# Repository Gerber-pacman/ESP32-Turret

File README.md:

# ESP32-Turret
Simple Stepper Motor Turret controled by esp32

For this project I have used Esp32 in a arduino uno shape.
For stepper motors I have used 2x ATD5833.
I have included PCB files, its a pretty simple pcb that connects everything nicely.

https://www.printables.com/model/1445566-laser-pointer-robot

If I forgot to include anything please let me know.
Have fun

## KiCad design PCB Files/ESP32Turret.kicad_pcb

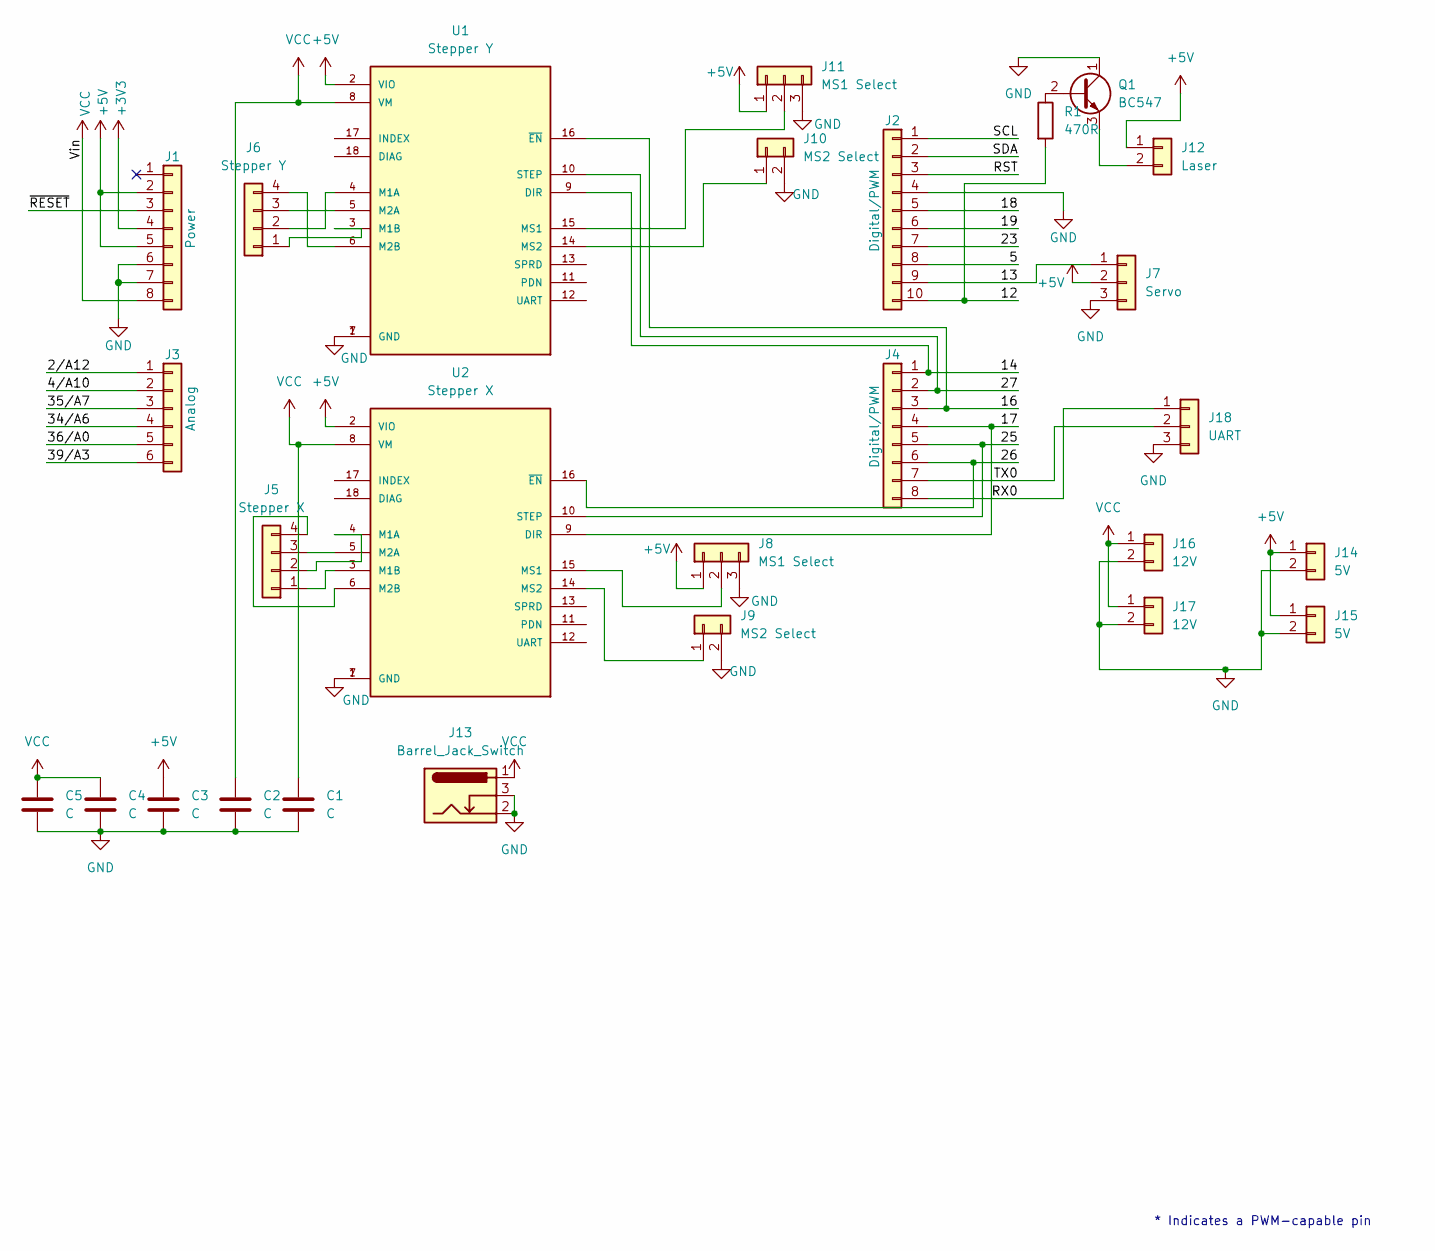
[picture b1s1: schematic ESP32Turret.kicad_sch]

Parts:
C1, C2, C3, C4, C5: C; CP_Radial_D6.3mm_P2.50mm
J1: Power; PinSocket_1x08_P2.54mm_Vertical
J2: Digital/PWM; PinSocket_1x10_P2.54mm_Vertical
J3: Analog; PinSocket_1x06_P2.54mm_Vertical
J4: Digital/PWM; PinSocket_1x08_P2.54mm_Vertical
J5: Stepper X; JST_XH_B4B-XH-A_1x04_P2.50mm_Vertical
J6: Stepper Y; JST_XH_B4B-XH-A_1x04_P2.50mm_Vertical
J7: Servo; PinHeader_1x03_P2.54mm_Vertical
J8, J11: MS1 Select; PinHeader_1x03_P2.54mm_Vertical
J9, J10: MS2 Select; PinHeader_1x02_P2.54mm_Vertical
J12: Laser; JST_EH_B2B-EH-A_1x02_P2.50mm_Vertical
J13: Barrel_Jack_Switch; BarrelJack_GCT_DCJ200-10-A_Horizontal
J14, J15: 5V; JST_EH_B2B-EH-A_1x02_P2.50mm_Vertical
J16, J17: 12V; JST_EH_B2B-EH-A_1x02_P2.50mm_Vertical
J18: UART; PinHeader_1x03_P2.54mm_Vertical
Q1: BC547; TO-92_Inline_Wide
R1: 470R; R_Axial_DIN0207_L6.3mm_D2.5mm_P10.16mm_Horizontal
U1: Stepper Y; MODULE_TMC2209_SILENTSTEPSTICK; PARTREV 1.20
U2: Stepper X; MODULE_TMC2209_SILENTSTEPSTICK; PARTREV 1.20

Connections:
+3V3: J1.4
+5V: C3.1, J1.2, J1.5, J7.2, J8.1, J11.1, J12.1, J14.1, J15.1, U1.2 (VIO), U2.2 (VIO)
/2/A12: J3.1
/4/A10: J3.2
/5: J2.8
/12: J2.10, R1.2
/13: J2.9, J7.1
/14: J4.1, U1.9 (DIR)
/16: J4.3, U1.16 (~EN)
/17: J4.4, U2.9 (DIR)
/18: J2.5
/19: J2.6
/23: J2.7
/25: J4.5, U2.10 (STEP)
/26: J4.6, U2.16 (~EN)
/27: J4.2, U1.10 (STEP)
/34/A6: J3.4
/35/A7: J3.3
/36/A0: J3.5
/39/A3: J3.6
/RST: J2.3
/RX0: J4.8, J18.1
/SCL: J2.1
/SDA: J2.2
/TX0: J4.7, J18.2
/~RESET: J1.3
GND: C1.2, C2.2, C3.2, C4.2, C5.2, J1.6, J1.7, J2.4, J7.3, J8.3, J9.2, J10.2, J11.3, J13.2, J13.3, J14.2, J15.2, J16.2, J17.2, J18.3, Q1.1 (C), U1.1 (GND), U1.7 (GND), U2.1 (GND), U2.7 (GND)
unnamed: J5.1, U2.3 (M1B)
unnamed: J5.2, U2.4 (M1A)
unnamed: J5.3, U2.5 (M2A)
unnamed: J5.4, U2.6 (M2B)
unnamed: J6.1, U1.3 (M1B)
unnamed: J6.2, U1.4 (M1A)
unnamed: J6.3, U1.5 (M2A)
unnamed: J6.4, U1.6 (M2B)
unnamed: J8.2, U2.15 (MS1)
unnamed: J9.1, U2.14 (MS2)
unnamed: J10.1, U1.14 (MS2)
unnamed: J11.2, U1.15 (MS1)
unnamed: J12.2, Q1.3 (E)
unnamed: Q1.2 (B), R1.1
VCC: C1.1, C2.1, C4.1, C5.1, J1.8, J13.1, J16.1, J17.1, U1.8 (VM), U2.8 (VM)

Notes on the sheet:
* Indicates a PWM-capable pin

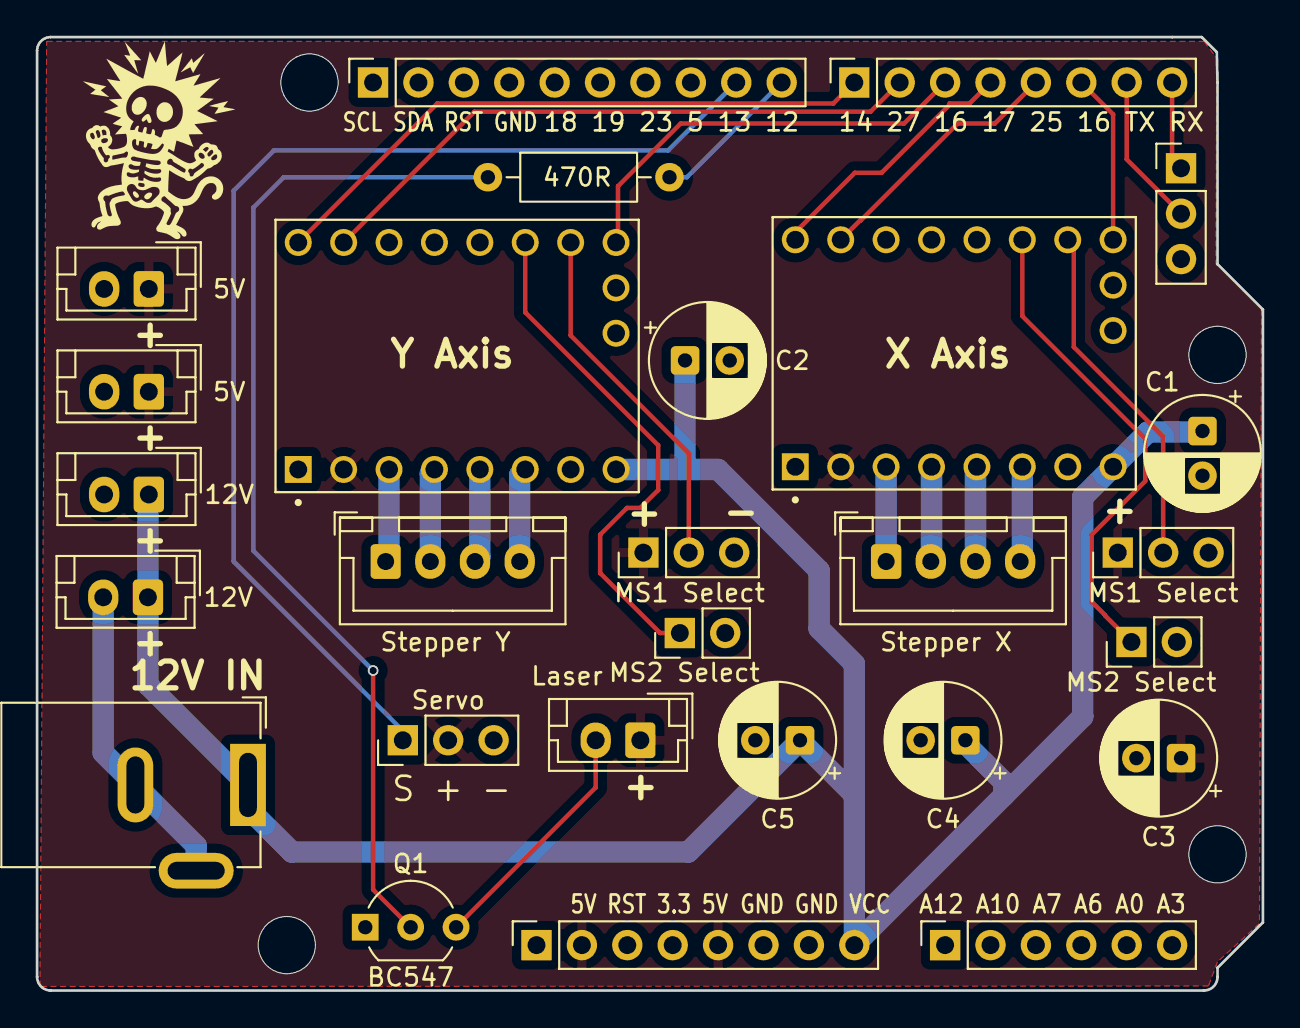
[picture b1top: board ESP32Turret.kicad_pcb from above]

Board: 2 copper layers, 68.6 x 53.3 mm, 31 parts (0 on the bottom side), 27 nets.

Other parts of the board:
MH1, MH2, MH3, MH4: MountingHole_3.2mm

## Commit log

2026-05-15 Update README with project details and images
    Added project details, images, and PCB file information.
2026-05-15 Fix link formatting in README.md
